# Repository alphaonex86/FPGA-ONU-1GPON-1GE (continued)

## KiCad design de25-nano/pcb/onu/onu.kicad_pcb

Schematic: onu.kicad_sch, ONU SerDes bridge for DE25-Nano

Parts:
C1, C3, C6, C9, C24, C25, C30, C48, C49, C50, C51, C54, C57, C60, C63, C65, C76, C77, C83, C85: 10u; C_0603_1608Metric
C2, C4, C5, C7, C8, C10, C11: 22u; C_0805_2012Metric
C12, C13, C66, C67: 1u; C_0402_1005Metric
C14, C15, C16, C17, C18, C19, C20, C21, C22, C23, C26, C27, C28, C29, C31, C32, C33, C34, C35, C36, C37, C38, C39, C40, C41, C42, C43, C44, C45, C46, C47, C52, C53, C55, C56, C58, C59, C61, C62, C64, C68, C69, C70, C71, C72, C73, C74, C75, C78, C79, C80, C81, C82, C84, C93, C94: 100n; C_0402_1005Metric
C86, C87: 100n; C_0603_1608Metric; MPN 100 V X7R
C88: 220p; C_0603_1608Metric; MPN 100 V X7R
C89: 47n; C_0402_1005Metric
C90: 2.2u; C_0603_1608Metric
C91, C92: 10p; C_0402_1005Metric
D1: BAT46WJ; D_SOD-323F; MPN BAT46WJ (100 V)
FB1, FB2, FB3, FB4, FB5, FB6, FB7, FB8, FB9: 120R@100MHz; L_0603_1608Metric; MPN BLM18PG121SN1D
H1, H2: M3; MountingHole_3.2mm_M3
J1: DE25-Nano GPIO; PinSocket_2x20_P2.54mm_Vertical
J2: JTAG; PinHeader_1x06_P2.54mm_Vertical
J3: OLT-ONU link; PinHeader_1x08_P2.54mm_Vertical
L1, L2: 2.2u; L_Cenker_CKCS252012; MPN CKCS252012-2R2M
L3: 4.7u; L_Cenker_CKCS252012; MPN 4.7 uH, Isat >= 1 A, 2520
R1, R3: 100k; R_0402_1005Metric
R2, R4: 120k; R_0402_1005Metric
R5, R6, R7, R8, R9, R12, R13, R14, R19, R20: 4.7k; R_0402_1005Metric
R10, R15, R16, R24, R26, R37, R43: 10k; R_0402_1005Metric
R11, R30, R35: 1k; R_0402_1005Metric
R17, R18: 0; R_0402_1005Metric
R21: 5.1k; R_0402_1005Metric
R22: 6.2k; R_0402_1005Metric
R23, R38: 20k; R_0402_1005Metric
R25: 12k; R_0402_1005Metric
R27: 5.6k; R_0402_1005Metric
R28: 3.9k; R_0402_1005Metric
R29, R41: 1.5k; R_0402_1005Metric
R31, R33, R40: 10; R_0402_1005Metric
R32: 15; R_0402_1005Metric
R34: 100; R_0402_1005Metric
R36: 300k; R_0603_1608Metric
R39: 33k; R_0402_1005Metric
R42: 3.01k; R_0402_1005Metric
RN1, RN2, RN3, RN4, RN5: 22; R_Array_Convex_4x0402; MPN 4D02WGJ0220TCE
U1, U2: TLV62569DBVR; SOT-23-5; MPN TLV62569DBVR
U3: TLV75525PDBVR; SOT-23-5; MPN TLV75525PDBVR
U4: LFE5UM-25F-6BG381C; Lattice_caBGA-381_17x17mm_Layout20x20_P0.8mm; MPN LFE5UM-25F-6BG381C
U5: SY88236LMG; QFN-32-1EP_5x5mm_P0.5mm_EP3.1x3.1mm_ThermalVias; MPN SY88236LMG
U6: SN65LVDT2DBVR; SOT-23-5; MPN SN65LVDT2DBVR
U7: BOSA GPON (X100DG); BOSA_GPON; MPN desoldered from an X100DG; pad order to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
U8: TPS61391RTER; WQFN-16-1EP_3x3mm_P0.5mm_EP1.68x1.68mm_ThermalVias; MPN TPS61391RTER
U9: AD5593RBRUZ; TSSOP-16_4.4x5mm_P0.65mm; MPN AD5593RBRUZ
Y1: SiT3821 155.52 MHz; Oscillator_SMD_SiTime_SiT9121-6Pin_3.2x2.5mm; MPN SiT3821AI-2B2-33NB155.520000 (LVDS, +-5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

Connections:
+1V1: C7.1, C8.1, C14.1, C15.1, C16.1, C17.1, C18.1, C19.1, C20.1, C21.1, C22.1, C23.1, C24.1, C25.1, L1.2, R1.1, U4.H8 (VCC), U4.H9 (VCC), U4.H10 (VCC), U4.H11 (VCC), U4.H12 (VCC), U4.H13 (VCC), U4.J8 (VCC), U4.J13 (VCC), U4.K8 (VCC), U4.K13 (VCC), U4.L8 (VCC), U4.L13 (VCC), U4.M8 (VCC), U4.M13 (VCC), U4.N8 (VCC), U4.N9 (VCC), U4.N10 (VCC), U4.N11 (VCC), U4.N12 (VCC), U4.N13 (VCC)
+1V1_HRX: C58.1, C59.1, C60.1, FB4.2, U4.T8 (VCCHRX0_D0CH0), U4.T9 (VCCHRX1_D0CH1)
+1V1_HTX: C55.1, C56.1, C57.1, FB3.2, U4.T7 (VCCHTX0_D0CH0), U4.T10 (VCCHTX1_D0CH1)
+1V1_SD: C10.1, C11.1, FB2.1, FB3.1, FB4.1, L2.2, R3.1
+1V1_VCCA: C52.1, C53.1, C54.1, FB2.2, U4.T6 (VCCA0), U4.U6 (VCCA0)
+2V5: C13.1, FB1.1, FB5.1, U3.5 (OUT)
+2V5_AUX: C26.1, C27.1, C28.1, C29.1, C30.1, FB1.2, U4.F6 (VCCAUX), U4.F15 (VCCAUX), U4.P6 (VCCAUX), U4.P15 (VCCAUX)
+2V5_AUXA: C61.1, C62.1, C63.1, FB5.2, U4.V10 (VCCAUXA0), U4.V11 (VCCAUXA0)
+3V3: C3.1, C4.1, C5.1, C12.1, C31.1, C32.1, C33.1, C34.1, C35.1, C36.1, C37.1, C38.1, C39.1, C40.1, C41.1, C42.1, C43.1, C44.1, C45.1, C46.1, C47.1, C48.1, C49.1, C50.1, C51.1, C94.1, FB6.1, FB7.1, FB9.1, J1.29, J2.1, R5.2, R6.2, R7.2, R8.2, R9.2, R10.2, R11.2, R12.2, R13.2, R19.2, R20.2, R43.2, U3.1 (IN), U3.3 (EN), U4.F9 (VCCIO0), U4.F10 (VCCIO0), U4.F11 (VCCIO1), U4.F12 (VCCIO1), U4.H6 (VCCIO7), U4.H7 (VCCIO7), U4.H14 (VCCIO2), U4.H15 (VCCIO2), U4.J6 (VCCIO7), U4.J15 (VCCIO2), U4.L6 (VCCIO6), U4.L7 (VCCIO6), U4.L14 (VCCIO3), U4.L15 (VCCIO3), U4.M6 (VCCIO6), U4.M15 (VCCIO3), U4.P9 (VCCIO8), U4.P10 (VCCIO8), U9.3 (V_{DD}), U9.9 (V_{LOGIC})
+3V3_APD: C84.1, C85.1, FB9.2, L3.1, R40.1, U8.10 (VIN), U8.13 (EN)
+3V3_APDA: C90.1, R40.2, U8.14 (AVCC), U8.15 (AVCC)
+3V3_OPT: C72.1, C73.1, C74.1, C75.1, C76.1, C77.1, C78.1, FB7.2, FB8.1, R21.2, R32.2, U5.17 (VCC), U5.20 (VCC), U5.32 (VCC), U6.1 (VCC), U7.T1 (LD_A), U7.T4 (MPD_K)
+3V3_RX: C81.1, C82.1, C83.1, FB8.2, U7.R2 (VCC)
+3V3_XO: C64.1, C65.1, FB6.2, Y1.6 (VDD)
+5V: C1.1, C2.1, C6.1, C9.1, J1.11, U1.1 (EN), U1.4 (VIN), U2.1 (EN), U2.4 (VIN)
APCFAULT_N: U5.25 (~APCFAULT), U9.13 (IO7)
APCSET: R23.1, R24.1, U5.12 (APCSET)
APC_ADJ: R24.2, U9.4 (IO0)
APD_ADJ: R38.2, U9.6 (IO2)
APD_CAP: C89.1, U8.9 (CAP)
APD_FB: R36.2, R37.1, R38.1, U8.12 (FB)
APD_ISHORT: R39.1, U8.11 (ISHORT)
APD_MON: C91.1, R41.1, U8.4 (MON1), U9.11 (IO5)
APD_MON2: C92.1, R42.1, U8.3 (MON2)
BEN0: J1.15, U4.A13 (PT40B)
BEN1: J1.17, U4.A12 (PT40A)
BEN2: J1.19, U4.A11 (PT27B/PCLKC0_1)
BEN3: J1.20, U4.B10 (PT24B/GR_PCLK0_0)
BEN4: J1.21, U4.A8 (PT18B)
BEN5: J1.22, U4.B9 (PT22A)
BEN6: J1.24, U4.B8 (PT15B)
BEN7: J1.26, U4.A7 (PT18A)
BEN_N: R18.1, U4.W9 (HDTXN0_D0CH1)
BEN_P: R17.1, U4.W8 (HDTXP0_D0CH1)
BIASMAX: R27.1, U5.14 (BIASMAX)
BIASMON: R29.1, U5.23 (BIASMON), U9.7 (IO3)
CCLK: J3.4, R11.1, U4.U3 (CCLK)
CFG0: R5.1, U4.U4 (CFG_0)
DDM_RESET: R43.1, U9.1 (~RESET)
DDM_VREF: C93.1, U9.8 (V_{REF})
DONE: R8.1, U4.Y3 (DONE)
DS0: J1.13, RN4.5 (R4.2)
DS0_S: RN4.4 (R4.1), U4.A14 (PT47A)
DS1: J1.14, RN4.6 (R3.2)
DS1_S: RN4.3 (R3.1), U4.B13 (PT42A)
DS2: J1.16, RN4.7 (R2.2)
DS2_S: RN4.2 (R2.1), U4.B12 (PT35A/PCLKT1_0)
DS3: J1.18, RN4.8 (R1.2)
DS3_S: RN4.1 (R1.1), U4.B11 (PT29A/PCLKT0_0)
DS4: J1.23, RN3.5 (R4.2)
DS4_S: RN3.4 (R4.1), U4.A9 (PT24A/GR_PCLK0_1)
DS5: J1.27, RN3.6 (R3.2)
DS5_S: RN3.3 (R3.1), U4.B6 (PT4B)
DS6: J1.28, RN3.7 (R2.2)
DS6_S: RN3.2 (R2.1), U4.A6 (PT4A)
DS7: J1.31, RN3.8 (R1.2)
DS7_S: RN3.1 (R1.1), U4.B5 (PL2C)
DS8: J1.32, RN2.5 (R4.2)
DS8_S: RN2.4 (R4.1), U4.A5 (PL2B)
DS9: J1.33, RN2.6 (R3.2)
DS9_S: RN2.3 (R3.1), U4.B4 (PL5B)
DS10: J1.34, RN2.7 (R2.2)
DS10_S: RN2.2 (R2.1), U4.A4 (PL2A)
DS11: J1.35, RN2.8 (R1.2)
DS11_S: RN2.1 (R1.1), U4.B3 (PL5D)
DS12: J1.36, RN1.5 (R4.2)
DS12_S: RN1.4 (R4.1), U4.A3 (PL5C)
DS13: J1.37, RN1.6 (R3.2)
DS13_S: RN1.3 (R3.1), U4.B2 (PL14C/VREF1_7)
DS14: J1.38, RN1.7 (R2.2)
DS14_S: RN1.2 (R2.1), U4.A2 (PL14A)
DS15: J1.39, RN1.8 (R1.2)
DS15_S: RN1.1 (R1.1), U4.B1 (PL14B)
DS_CLK: J1.1, RN5.7 (R2.2)
DS_CLK_S: RN5.2 (R2.1), U4.B20 (PT67B)
FB_1V1: R1.2, R2.1, U1.5 (FB)
FB_1V1_SD: R3.2, R4.1, U2.5 (FB)
GND: C1.2, C2.2, C3.2, C4.2, C5.2, C6.2, C7.2, C8.2, C9.2, C10.2, C11.2, C12.2, C13.2, C14.2, C15.2, C16.2, C17.2, C18.2, C19.2, C20.2, C21.2, C22.2, C23.2, C24.2, C25.2, C26.2, C27.2, C28.2, C29.2, C30.2, C31.2, C32.2, C33.2, C34.2, C35.2, C36.2, C37.2, C38.2, C39.2, C40.2, C41.2, C42.2, C43.2, C44.2, C45.2, C46.2, C47.2, C48.2, C49.2, C50.2, C51.2, C52.2, C53.2, C54.2, C55.2, C56.2, C57.2, C58.2, C59.2, C60.2, C61.2, C62.2, C63.2, C64.2, C65.2, C66.2, C67.2, C72.2, C73.2, C74.2, C75.2, C76.2, C77.2, C78.2, C81.2, C82.2, C83.2, C84.2, C85.2, C86.2, C87.2, C88.2, C89.2, C90.2, C91.2, C92.2, C93.2, C94.2, J1.12, J1.30, J2.6, J3.1, J3.8, R2.2, R4.2, R14.2, R22.2, R23.2, R25.2, R27.2, R28.2, R29.2, R30.2, R37.2, R39.2, R41.2, R42.2, U1.2 (GND), U2.2 (GND), U3.2 (GND), U4.B7 (GND), U4.B14 (GND), U4.C19 (GND), U4.D4 (GND), U4.F7 (GND), U4.F8 (GND), U4.F13 (GND), U4.F14 (GND), U4.G4 (GND), U4.G6 (GND), U4.G7 (GND), U4.G8 (GND), U4.G9 (GND), U4.G10 (GND), U4.G11 (GND), U4.G12 (GND), U4.G13 (GND), U4.G14 (GND), U4.G15 (GND), U4.G17 (GND), U4.H19 (GND), U4.J2 (GND), U4.J7 (GND), U4.J9 (GND), U4.J10 (GND), U4.J11 (GND), U4.J12 (GND), U4.J14 (GND), U4.K6 (GND), U4.K7 (GND), U4.K9 (GND), U4.K10 (GND), U4.K11 (GND), U4.K12 (GND), U4.K14 (GND), U4.K15 (GND), U4.L9 (GND), U4.L10 (GND), U4.L11 (GND), U4.L12 (GND), U4.M2 (GND), U4.M7 (GND), U4.M9 (GND), U4.M10 (GND), U4.M11 (GND), U4.M12 (GND), U4.M14 (GND), U4.M16 (GND), U4.N6 (GND), U4.N7 (GND), U4.N14 (GND), U4.N15 (GND), U4.P7 (GND), U4.P8 (GND), U4.P11 (GND), U4.P12 (GND), U4.P13 (GND), U4.P14 (GND), U4.R4 (CFG_2), U4.R19 (GND), U4.T4 (CFG_1), U4.U7 (GND), U4.U8 (GND), U4.U9 (GND), U4.U10 (GND), U4.U11 (GND), U4.U12 (GND), U4.U13 (GND), U4.U14 (GND), U4.V5 (GND), U4.V6 (GND), U4.V7 (GND), U4.V8 (GND), U4.V9 (GND), U4.V12 (GND), U4.V13 (GND), U4.V14 (GND), U4.V15 (GND), U4.V16 (GND), U4.V19 (GND), U4.V20 (GND), U4.W6 (GND), U4.W7 (GND), U4.W12 (GND), U4.W15 (GND), U4.W16 (GND), U4.W19 (GND), U4.Y7 (HDRXP0_D0CH1), U4.Y8 (HDRXN0_D0CH1), U5.1 (LOS/SD_SEL), U5.5 (GND), U5.8 (GND), U5.16 (GND), U5.24 (GND), U5.29 (GND), U5.33 (EP), U6.2 (GND), U7.R5 (GND), U8.7 (GND), U8.16 (AGND), U8.17 (EP), U9.2 (A0), U9.14 (GND), Y1.3 (GND)
HOLDN: R10.1, U4.R2 (PB15A/HOLDN/DI/BUSY/CSSPIN/CEN)
HV_APD: C88.1, U7.R1 (VAPD), U8.5 (APD)
HV_FILT: C87.1, R34.2, R35.1
HV_MONIN: R35.2, U8.6 (MONIN)
HV_OUT: C86.1, D1.1 (K), R34.1, R36.1
HV_SW: D1.2 (A), L3.2, U8.8 (SW)
INITN: R7.1, U4.V3 (INITN)
LASER_DIS: R19.1, U4.U17 (PR47B), U5.11 (TXDIS)
LD_BEN: U5.9 (BEN+), U6.5 (R)
LD_BEN_N: R22.1, U5.10 (BEN-)
LD_BIAS: R33.1, U5.21 (BIAS)
LD_K: R31.2, R33.2, U7.T2 (LD_K)
LD_MD: U5.22 (MD), U7.T3 (MPD_A)
LD_MODN: R32.1, U5.18 (MOD-)
LD_MODP: R31.1, U5.19 (MOD+)
LOSLVL: R21.1, U5.2 (LOSLVL)
MISO: J3.6, U4.V2 (PB11A/D1/MISO/IO1)
MODMON: R28.1, U5.15 (MODMON), U9.10 (IO4)
MODSET: R25.1, R26.1, U5.13 (MODSET)
MOD_ADJ: R26.2, U9.5 (IO1)
MOSI: J3.5, U4.W2 (PB11B/D0/MOSI/IO0)
ONU_BEN_N: R18.2, U6.4 (B)
ONU_BEN_P: R17.2, U6.3 (A)
ONU_PROGRAMN: J3.7, R6.1, U4.W3 (PROGRAMN)
ONU_RD_N: C71.1, U5.30 (ROUT-)
ONU_RD_P: C70.1, U5.31 (ROUT+)
ONU_SCL: J3.2, U9.16 (SCL)
ONU_SDA: J3.3, U9.15 (SDA)
ONU_TD_N: C69.2, U5.6 (DIN+)
ONU_TD_P: C68.2, U5.7 (DIN-)
REFCLK_N: U4.Y12 (REFCLKN_D0), Y1.5 (OUT-)
REFCLK_P: U4.Y11 (REFCLKP_D0), Y1.4 (OUT+)
RIN_N: C80.2, U5.28 (RIN-)
RIN_P: C79.2, U5.27 (RIN+)
RSSI: R30.1, U5.26 (RSSI), U9.12 (IO6)
RX0_N: C71.2, U4.Y6 (HDRXN0_D0CH0)
RX0_P: C70.2, U4.Y5 (HDRXP0_D0CH0)
RX_SD: R20.1, U4.T17 (PR47D/LRC_GPLL0C_IN), U5.3 (LOS/SD), U5.4 (~JAM)
SN: J1.40, R9.1, U4.T2 (PB13A/SN/CSN)
SW_1V1: L1.1, U1.3 (SW)
SW_1V1_SD: L2.1, U2.3 (SW)
TCK: J2.2, R14.1, U4.T5 (TCK)
TDI: J2.3, R12.1, U4.R5 (TDI)
TDO: J2.4, U4.V4 (TDO)
TIA_N: C80.1, U7.R4 (OUT-)
TIA_P: C79.1, U7.R3 (OUT+)
TMS: J2.5, R13.1, U4.U5 (TMS)
TX0_N: C69.1, U4.W5 (HDTXN0_D0CH0)
TX0_P: C68.1, U4.W4 (HDTXP0_D0CH0)
TX_CLK: J1.3, RN5.8 (R1.2)
TX_CLK_S: RN5.1 (R1.1), U4.A19 (PT67A)
US0: J1.2, U4.B19 (PT65B)
US1: J1.4, U4.B18 (PT62B)
US2: J1.5, U4.A18 (PT65A)
US3: J1.6, U4.B17 (PT60A)
US4: J1.7, U4.A17 (PT62A)
US5: J1.8, U4.B16 (PT56B)
US6: J1.9, U4.A16 (PT56A)
US7: J1.10, U4.B15 (PT51A)
US_CLK: J1.25, U4.A10 (PT27A/PCLKT0_1)
VCXO_PWM: R15.1, U4.U16 (PR47C/LRC_GPLL0T_IN)
VCXO_RC: C66.1, R15.2, R16.1
VCXO_VC: C67.1, R16.2, Y1.1 (VIN)

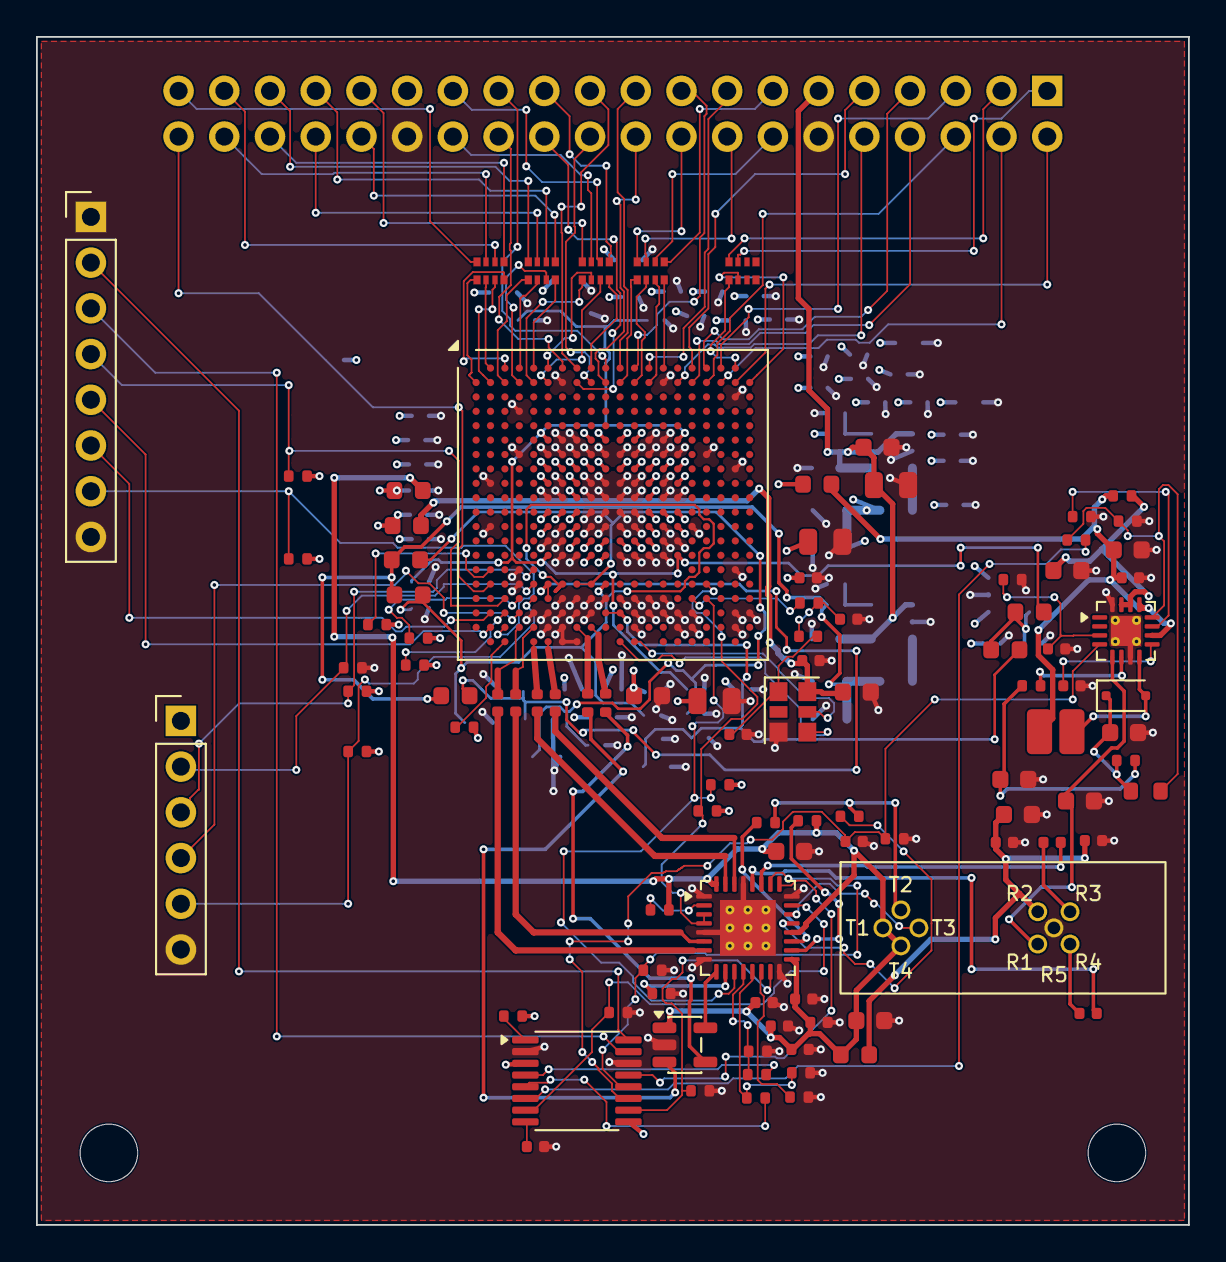
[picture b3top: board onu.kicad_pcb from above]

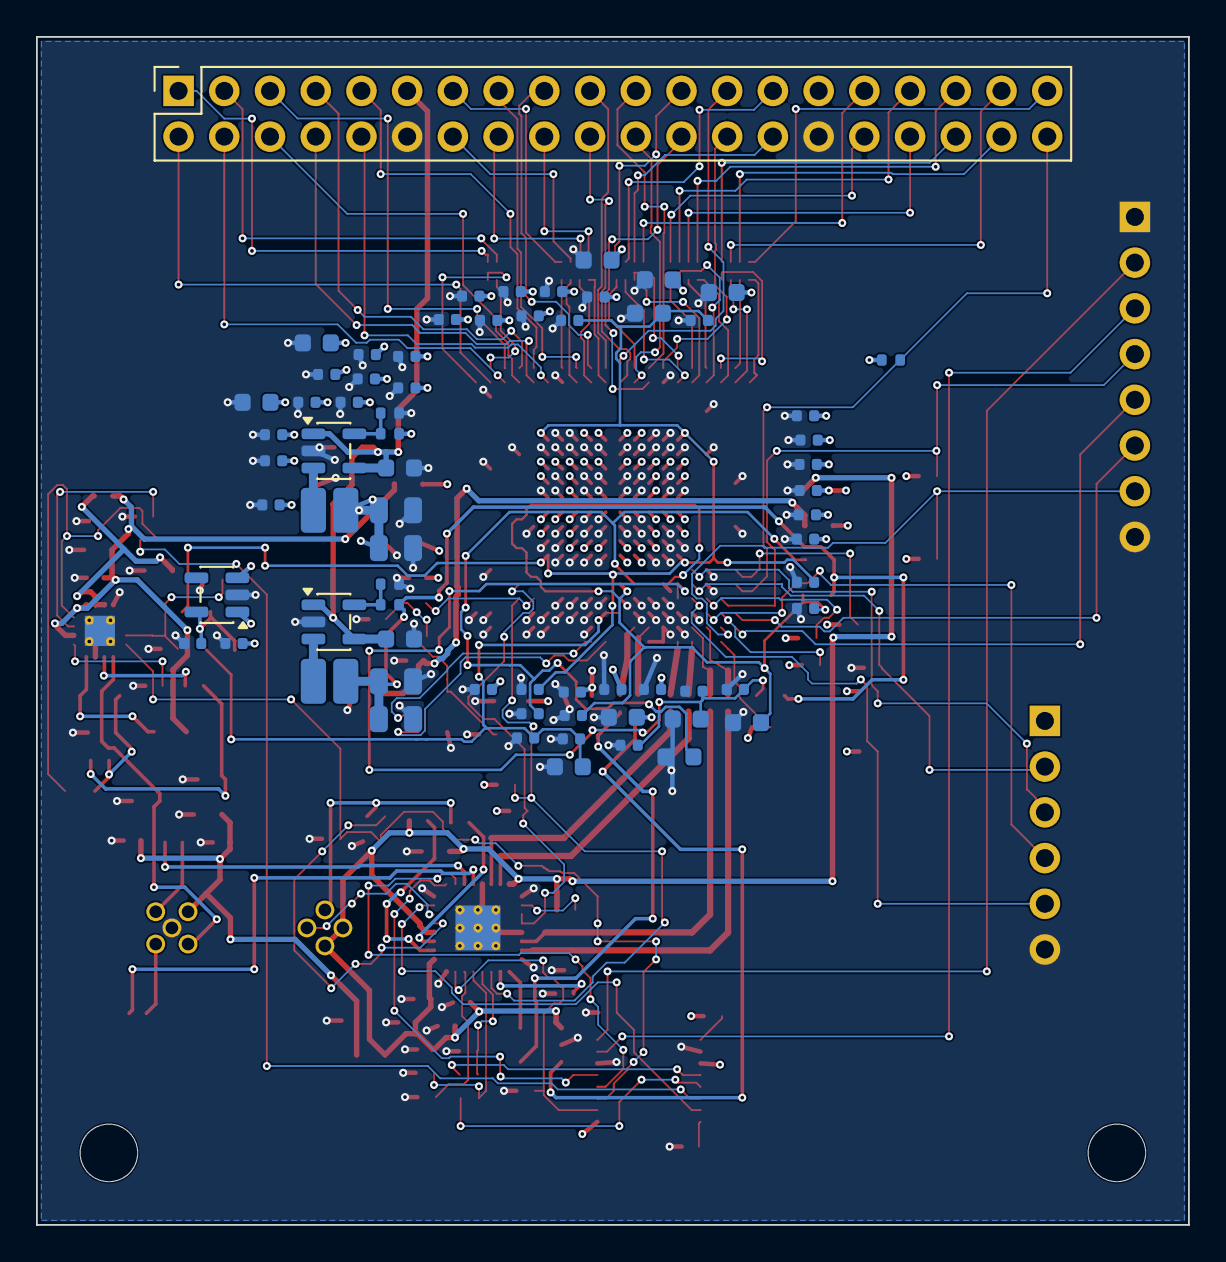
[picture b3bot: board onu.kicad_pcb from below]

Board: 4 copper layers, 64.0 x 66.0 mm, 170 parts (69 on the bottom side), 141 nets.

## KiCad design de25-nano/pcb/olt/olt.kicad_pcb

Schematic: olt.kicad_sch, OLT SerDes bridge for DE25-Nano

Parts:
C1, C3, C6, C9, C24, C25, C30, C48, C49, C50, C51, C54, C57, C60, C63, C66, C72, C74: 10u; C_0603_1608Metric
C2, C4, C5, C7, C8, C10, C11, C75: 22u; C_0805_2012Metric
C12, C13: 1u; C_0402_1005Metric
C14, C15, C16, C17, C18, C19, C20, C21, C22, C23, C26, C27, C28, C29, C31, C32, C33, C34, C35, C36, C37, C38, C39, C40, C41, C42, C43, C44, C45, C46, C47, C52, C53, C55, C56, C58, C59, C61, C62, C64, C65, C67, C68, C69, C70, C71, C73: 100n; C_0402_1005Metric
FB1, FB2, FB3, FB4, FB5, FB6: 120R@100MHz; L_0603_1608Metric; MPN BLM18PG121SN1D
H1, H2: M3; MountingHole_3.2mm_M3
J1: DE25-Nano GPIO; PinSocket_2x20_P2.54mm_Vertical
J2: JTAG; PinHeader_1x06_P2.54mm_Vertical
J3: SFP cage; Connector_SFP_and_Cage; MPN TE 1367073-1 + cage 2227302-1
J4: OLT-ONU link; PinHeader_1x08_P2.54mm_Vertical
L1, L2: 2.2u; L_Cenker_CKCS252012; MPN SLO252012F2R2MTT
L3, L4: 1u; L_0805_2012Metric; MPN 1 uH >= 1 A, low DCR
R1, R3: 100k; R_0402_1005Metric
R2, R4: 120k; R_0402_1005Metric
R5, R6, R7, R8, R9, R12, R13, R14, R21, R22, R27, R28, R29, R30, R31, R32: 4.7k; R_0402_1005Metric
R10, R15, R16, R17, R20, R23, R24: 10k; R_0402_1005Metric
R11: 1k; R_0402_1005Metric
R18, R19: 2.2k; R_0402_1005Metric
R25: 33; R_0402_1005Metric
R26: 330; R_0402_1005Metric
RN1, RN2, RN3: 22; R_Array_Convex_4x0402; MPN 4D02WGJ0220TCE
U1, U2: TLV62569DBVR; SOT-23-5; MPN TLV62569DBVR
U3: TLV75525PDBVR; SOT-23-5; MPN TLV75525PDBVR
U4: LFE5UM-25F-6BG381C; Lattice_caBGA-381_17x17mm_Layout20x20_P0.8mm; MPN LFE5UM-25F-6BG381C
U5: PCA9555PW; TSSOP-24_4.4x7.8mm_P0.65mm; MPN PCA9555PW
U6: PCA9540BD; SOIC-8_3.9x4.9mm_P1.27mm; MPN PCA9540BD
U7, U8: SN74LVC1G125DBVR; SOT-23-5; MPN SN74LVC1G125DBVR
Y1: SiT9121 155.52 MHz; Oscillator_SMD_SiTime_SiT9121-6Pin_3.2x2.5mm; MPN SiT9121AI-2B3-33E155.52000 (LVDS; check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
Y2: SiT9121 125 MHz; Oscillator_SMD_SiTime_SiT9121-6Pin_3.2x2.5mm; MPN SiT9121AI-2B3-33E125000 (LVDS; check co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

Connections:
+1V1: C7.1, C8.1, C14.1, C15.1, C16.1, C17.1, C18.1, C19.1, C20.1, C21.1, C22.1, C23.1, C24.1, C25.1, L1.2, R1.1, U4.H8 (VCC), U4.H9 (VCC), U4.H10 (VCC), U4.H11 (VCC), U4.H12 (VCC), U4.H13 (VCC), U4.J8 (VCC), U4.J13 (VCC), U4.K8 (VCC), U4.K13 (VCC), U4.L8 (VCC), U4.L13 (VCC), U4.M8 (VCC), U4.M13 (VCC), U4.N8 (VCC), U4.N9 (VCC), U4.N10 (VCC), U4.N11 (VCC), U4.N12 (VCC), U4.N13 (VCC)
+1V1_HRX: C58.1, C59.1, C60.1, FB4.2, U4.T8 (VCCHRX0_D0CH0)
+1V1_HTX: C55.1, C56.1, C57.1, FB3.2, U4.T7 (VCCHTX0_D0CH0), U4.T10 (VCCHTX1_D0CH1)
+1V1_SD: C10.1, C11.1, FB2.1, FB3.1, FB4.1, L2.2, R3.1
+1V1_VCCA: C52.1, C53.1, C54.1, FB2.2, U4.T6 (VCCA0), U4.U6 (VCCA0)
+2V5: C13.1, FB1.1, FB5.1, U3.5 (OUT)
+2V5_AUX: C26.1, C27.1, C28.1, C29.1, C30.1, FB1.2, U4.F6 (VCCAUX), U4.F15 (VCCAUX), U4.P6 (VCCAUX), U4.P15 (VCCAUX)
+2V5_AUXA: C61.1, C62.1, C63.1, FB5.2, U4.V10 (VCCAUXA0), U4.V11 (VCCAUXA0)
+3V3: C3.1, C4.1, C5.1, C12.1, C31.1, C32.1, C33.1, C34.1, C35.1, C36.1, C37.1, C38.1, C39.1, C40.1, C41.1, C42.1, C43.1, C44.1, C45.1, C46.1, C47.1, C48.1, C49.1, C50.1, C51.1, C67.1, C68.1, C69.1, C70.1, C75.1, FB6.1, J1.29, J2.1, L3.1, L4.1, R5.2, R6.2, R7.2, R8.2, R9.2, R10.2, R11.2, R12.2, R13.2, R15.2, R16.2, R18.2, R19.2, R20.2, R21.2, R22.2, R23.2, R24.2, R27.2, R28.2, R29.2, R30.2, R31.2, R32.2, U3.1 (IN), U3.3 (EN), U4.F9 (VCCIO0), U4.F10 (VCCIO0), U4.F11 (VCCIO1), U4.F12 (VCCIO1), U4.H6 (VCCIO7), U4.H7 (VCCIO7), U4.H14 (VCCIO2), U4.H15 (VCCIO2), U4.J6 (VCCIO7), U4.J15 (VCCIO2), U4.L6 (VCCIO6), U4.L7 (VCCIO6), U4.L14 (VCCIO3), U4.L15 (VCCIO3), U4.M6 (VCCIO6), U4.M15 (VCCIO3), U4.P9 (VCCIO8), U4.P10 (VCCIO8), U5.24 (VDD), U6.3 (VDD), U7.5 (VCC), U8.5 (VCC)
+3V3_SFPR: C73.1, C74.1, J3.15 (VccR), L4.2
+3V3_SFPT: C71.1, C72.1, J3.16 (VccT), L3.2
+3V3_XO: C64.1, C65.1, C66.1, FB6.2, Y1.6 (VDD), Y2.6 (VDD)
+5V: C1.1, C2.1, C6.1, C9.1, J1.11, U1.1 (EN), U1.4 (VIN), U2.1 (EN), U2.4 (VIN)
AUX: J1.16, RN1.8 (R1.2)
AUX_S: RN1.1 (R1.1), U4.A10 (PT27A/PCLKT0_1)
CCLK: J1.37, J4.4, R11.1, U4.U3 (CCLK)
CFG0: R5.1, U4.U4 (CFG_0)
DONE: R8.1, U4.Y3 (DONE)
DS0: J1.3, U4.B18 (PT62B)
DS1: J1.13, U4.A12 (PT40A)
DS2: J1.14, U4.B11 (PT29A/PCLKT0_0)
DS3: J1.15, U4.A11 (PT27B/PCLKC0_1)
DS4: J1.23, U4.A9 (PT24A/GR_PCLK0_1)
DS5: J1.24, U4.A8 (PT18B)
DS6: J1.25, U4.A7 (PT18A)
DS7: J1.26, U4.B6 (PT4B)
DS8: J1.27, U4.A6 (PT4A)
DS9: J1.28, U4.A5 (PL2B)
DS10: J1.31, U4.B4 (PL5B)
DS11: J1.32, U4.A4 (PL2A)
DS12: J1.33, U4.A3 (PL5C)
DS13: J1.34, U4.B2 (PL14C/VREF1_7)
DS14: J1.35, U4.A2 (PL14A)
DS15: J1.36, U4.B1 (PL14B)
DS_CLK: J1.22, U4.B12 (PT35A/PCLKT1_0)
FB_1V1: R1.2, R2.1, U1.5 (FB)
FB_1V1_SD: R3.2, R4.1, U2.5 (FB)
GND: C1.2, C2.2, C3.2, C4.2, C5.2, C6.2, C7.2, C8.2, C9.2, C10.2, C11.2, C12.2, C13.2, C14.2, C15.2, C16.2, C17.2, C18.2, C19.2, C20.2, C21.2, C22.2, C23.2, C24.2, C25.2, C26.2, C27.2, C28.2, C29.2, C30.2, C31.2, C32.2, C33.2, C34.2, C35.2, C36.2, C37.2, C38.2, C39.2, C40.2, C41.2, C42.2, C43.2, C44.2, C45.2, C46.2, C47.2, C48.2, C49.2, C50.2, C51.2, C52.2, C53.2, C54.2, C55.2, C56.2, C57.2, C58.2, C59.2, C60.2, C61.2, C62.2, C63.2, C64.2, C65.2, C66.2, C67.2, C68.2, C69.2, C70.2, C71.2, C72.2, C73.2, C74.2, C75.2, J1.12, J1.30, J2.6, J3.1 (VeeT), J3.10 (VeeR), J3.11 (VeeR), J3.14 (VeeR), J3.17 (VeeT), J3.20 (VeeT), J3.CAGE, J4.1, J4.8, R2.2, R4.2, R14.2, R17.2, U1.2 (GND), U2.2 (GND), U3.2 (GND), U4.B7 (GND), U4.B14 (GND), U4.C19 (GND), U4.D4 (GND), U4.F7 (GND), U4.F8 (GND), U4.F13 (GND), U4.F14 (GND), U4.G4 (GND), U4.G6 (GND), U4.G7 (GND), U4.G8 (GND), U4.G9 (GND), U4.G10 (GND), U4.G11 (GND), U4.G12 (GND), U4.G13 (GND), U4.G14 (GND), U4.G15 (GND), U4.G17 (GND), U4.H19 (GND), U4.J2 (GND), U4.J7 (GND), U4.J9 (GND), U4.J10 (GND), U4.J11 (GND), U4.J12 (GND), U4.J14 (GND), U4.K6 (GND), U4.K7 (GND), U4.K9 (GND), U4.K10 (GND), U4.K11 (GND), U4.K12 (GND), U4.K14 (GND), U4.K15 (GND), U4.L9 (GND), U4.L10 (GND), U4.L11 (GND), U4.L12 (GND), U4.M2 (GND), U4.M7 (GND), U4.M9 (GND), U4.M10 (GND), U4.M11 (GND), U4.M12 (GND), U4.M14 (GND), U4.M16 (GND), U4.N6 (GND), U4.N7 (GND), U4.N14 (GND), U4.N15 (GND), U4.P7 (GND), U4.P8 (GND), U4.P11 (GND), U4.P12 (GND), U4.P13 (GND), U4.P14 (GND), U4.R4 (CFG_2), U4.R19 (GND), U4.T4 (CFG_1), U4.U7 (GND), U4.U8 (GND), U4.U9 (GND), U4.U10 (GND), U4.U11 (GND), U4.U12 (GND), U4.U13 (GND), U4.U14 (GND), U4.V5 (GND), U4.V6 (GND), U4.V7 (GND), U4.V8 (GND), U4.V9 (GND), U4.V12 (GND), U4.V13 (GND), U4.V14 (GND), U4.V15 (GND), U4.V16 (GND), U4.V19 (GND), U4.V20 (GND), U4.W6 (GND), U4.W7 (GND), U4.W12 (GND), U4.W15 (GND), U4.W16 (GND), U4.W19 (GND), U4.Y7 (HDRXP0_D0CH1), U4.Y8 (HDRXN0_D0CH1), U5.2 (A1), U5.3 (A2), U5.12 (VSS), U5.21 (A0), U6.6 (VSS), U7.3 (GND), U8.3 (GND), Y1.3 (GND), Y2.3 (GND)
HOLDN: R10.1, U4.R2 (PB15A/HOLDN/DI/BUSY/CSSPIN/CEN)
INITN: R7.1, U4.V3 (INITN)
IRQ: J1.21, R20.1, U5.1 (~INT)
MISO: J1.40, J4.6, R15.1, U4.V2 (PB11A/D1/MISO/IO1)
MOSI: J1.39, J4.5, U4.W2 (PB11B/D0/MOSI/IO0)
OLT_PROGRAMN: R6.1, U4.W3 (PROGRAMN), U5.13 (IO1_0)
ONU_PROGRAMN: J4.7, U5.14 (IO1_1)
ONU_SCL: J4.2, R21.1, U6.8 (SC1)
ONU_SDA: J4.3, R22.1, U6.7 (SD1)
P7_BUF: R25.1, U7.4
P7_OE_N: R23.1, U5.8 (IO0_4), U7.1
P9_BUF: R26.1, U8.4
P9_OE_N: R24.1, U5.9 (IO0_5), U8.1
REF125_OE: R17.1, U5.11 (IO0_7), Y2.1 (OE)
REF155_OE: R16.1, U5.10 (IO0_6), Y1.1 (OE)
REFCLK_N: U4.Y12 (REFCLKN_D0), Y1.5 (OUT-), Y2.5 (OUT-)
REFCLK_P: U4.Y11 (REFCLKP_D0), Y1.4 (OUT+), Y2.4 (OUT+)
RSSI_TRIG: J1.18, U8.2
RX0_N: J3.12 (RD-), U4.Y6 (HDRXN0_D0CH0)
RX0_P: J3.13 (RD+), U4.Y5 (HDRXP0_D0CH0)
RX_RESET: J1.17, U7.2
SCL: J1.19, R18.1, U5.22 (SCL), U6.1 (SCL)
SDA: J1.20, R19.1, U5.23 (SDA), U6.2 (SDA)
SFP_LOS: J3.8 (RX_LOS), R29.1, U5.6 (IO0_2)
SFP_MOD_ABS: J3.6 (MOD_ABS), R30.1, U5.4 (IO0_0)
SFP_P7: J3.7 (RS0), R25.2
SFP_P9: J3.9 (RS1), R26.2
SFP_SCL: J3.5 (SCL), R31.1, U6.5 (SC0)
SFP_SDA: J3.4 (SDA), R32.1, U6.4 (SD0)
SFP_TX_DIS: J3.3 (TX_DISABLE), R28.1, U5.7 (IO0_3)
SFP_TX_FAULT: J3.2 (TX_FAULT), R27.1, U5.5 (IO0_1)
SN: J1.38, R9.1, U4.T2 (PB13A/SN/CSN)
SW_1V1: L1.1, U1.3 (SW)
SW_1V1_SD: L2.1, U2.3 (SW)
TCK: J2.2, R14.1, U4.T5 (TCK)
TDI: J2.3, R12.1, U4.R5 (TDI)
TDO: J2.4, U4.V4 (TDO)
TMS: J2.5, R13.1, U4.U5 (TMS)
TX0_N: J3.18 (TD+), U4.W5 (HDTXN0_D0CH0)
TX0_P: J3.19 (TD-), U4.W4 (HDTXP0_D0CH0)
TX_CLK: J1.1, RN3.7 (R2.2)
TX_CLK_S: RN3.2 (R2.1), U4.B19 (PT65B)
US0: J1.2, RN3.8 (R1.2)
US0_S: RN3.1 (R1.1), U4.A19 (PT67A)
US1: J1.4, RN2.5 (R4.2)
US1_S: RN2.4 (R4.1), U4.B17 (PT60A)
US2: J1.5, RN2.6 (R3.2)
US2_S: RN2.3 (R3.1), U4.A17 (PT62A)
US3: J1.6, RN2.7 (R2.2)
US3_S: RN2.2 (R2.1), U4.B16 (PT56B)
US4: J1.7, RN2.8 (R1.2)
US4_S: RN2.1 (R1.1), U4.B15 (PT51A)
US5: J1.8, RN1.5 (R4.2)
US5_S: RN1.4 (R4.1), U4.A14 (PT47A)
US6: J1.9, RN1.6 (R3.2)
US6_S: RN1.3 (R3.1), U4.B13 (PT42A)
US7: J1.10, RN1.7 (R2.2)
US7_S: RN1.2 (R2.1), U4.A13 (PT40B)

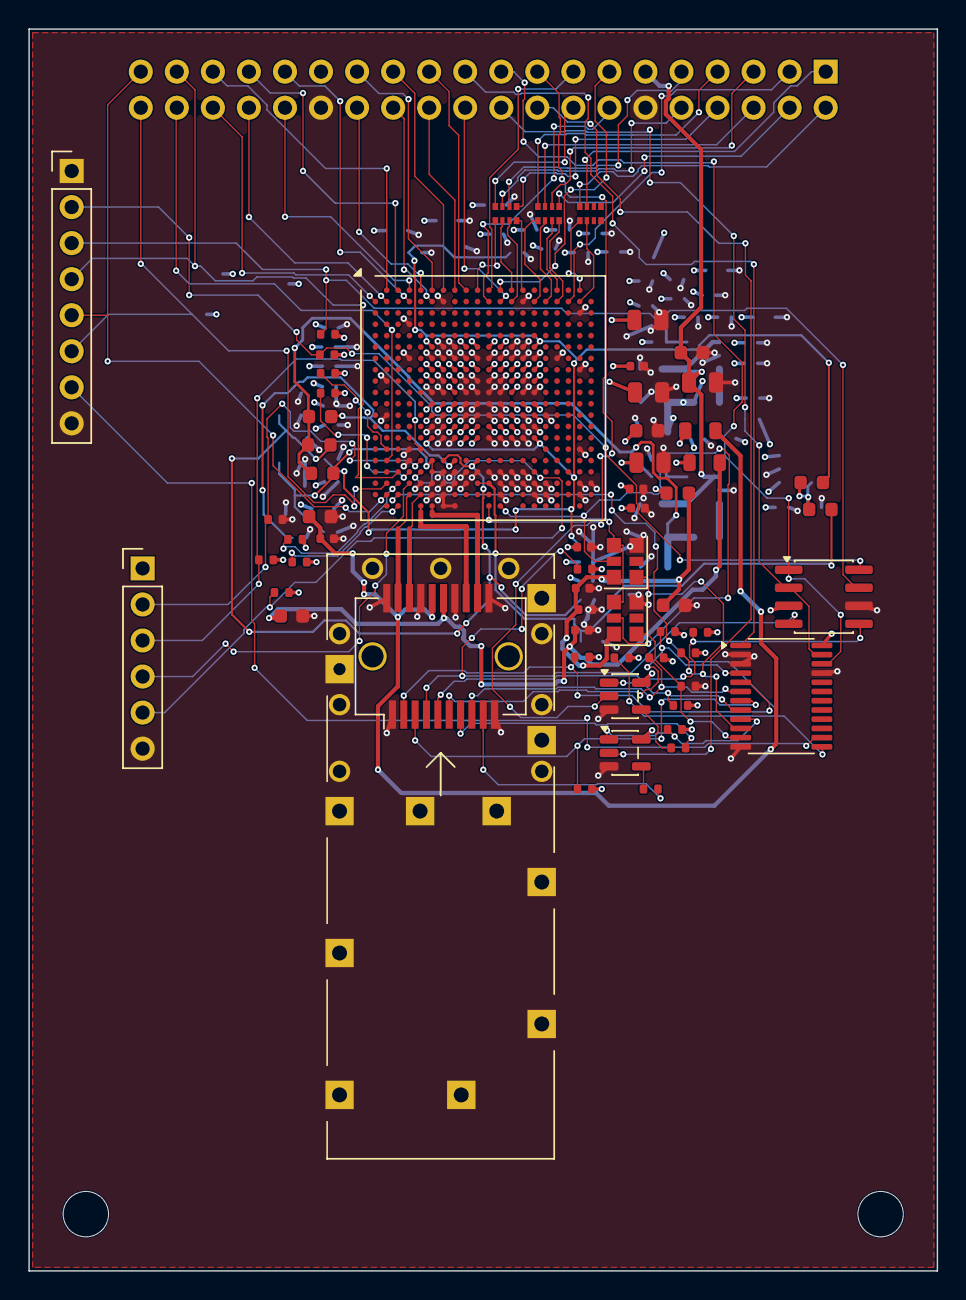
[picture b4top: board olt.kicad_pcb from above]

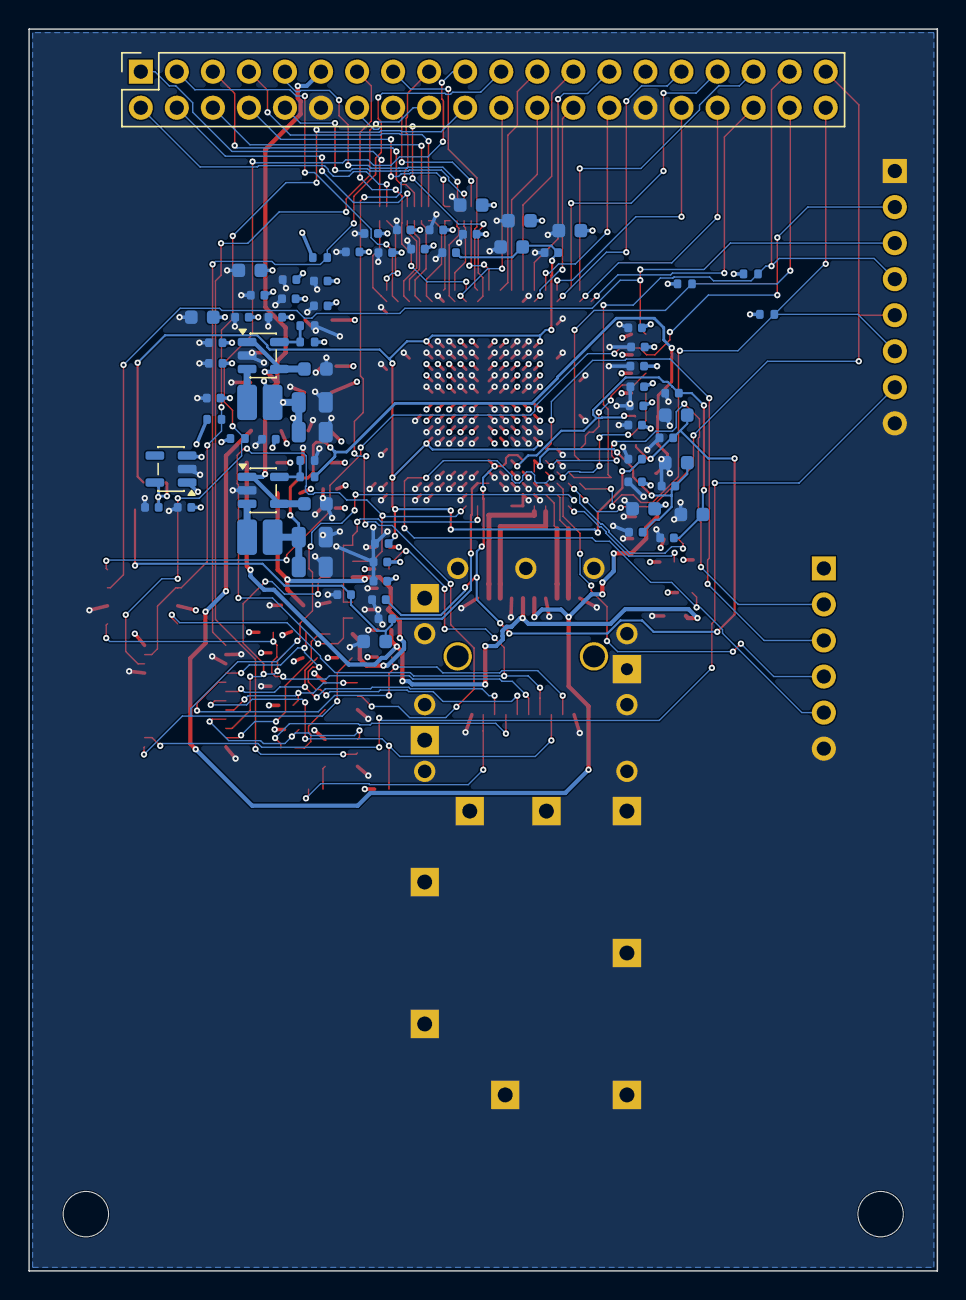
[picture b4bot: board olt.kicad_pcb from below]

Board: 4 copper layers, 64.0 x 87.5 mm, 136 parts (74 on the bottom side), 96 nets.

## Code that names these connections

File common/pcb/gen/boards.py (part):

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        cfg = {'CFG_0': 'GND', 'CFG_1': 'GND', 'CFG_2': 'GND', 'PROGRAMN': programn, 'INITN': 'INITN', 'DONE': 'DONE',
               'TCK': 'TCK', 'TDI': 'TDI', 'TDO': 'TDO', 'TMS': 'TMS', 'CCLK': spi[1]}
        cfg[f'CFG_{mode[-1]}'] = mode
        select, idle = ('HOLDN/DI/BUSY/CSSPIN/CEN', 'SN/CSN') if flash else ('SN/CSN', 'HOLDN/DI/BUSY/CSSPIN/CEN')
        dual = {select: spi[0], 'D0/MOSI/IO0': spi[2], 'D1/MISO/IO1': spi[3], idle: 'HOLDN'}
        for b, f in all_balls.items():
            if f in cfg: conn[b] = cfg[f]
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          {'A': 'ONU_BEN_P', 'B': 'ONU_BEN_N', 'R': 'LD_BEN', 'VCC': '+3V3_OPT', 'GND': 'GND'}, MPN='SN65LVDT2DBVR')
    b.decouple('+3V3_OPT', 1)
    b.r('6.2k', 'LD_BEN_N', 'GND')    # BEN- threshold for LVTTL on BEN+ (datasheet Fig. 2e)
    for pin, r_gnd, dac in (('APCSET', '20k', 'APC_ADJ'), ('MODSET', '12k', 'MOD_ADJ')):
        b.r(r_gnd, pin, 'GND'); b.r('10k', pin, dac)
    b.r('5.6k', 'BIASMAX', 'GND')
    b.r('3.9k', 'MODMON', 'GND'); b.r('1.5k', 'BIASMON', 'GND'); b.r('1k', 'RSSI', 'GND')   # <= 2.5 V ADC, RSSI < 1.2 V
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    return b

def sfp_cage(b, name, td, rd, vcc='+3V3'):
    """SFP/SFP+ cage, own I2C bus; RS0/RS1 (OLT modules: Rx_Reset / RSSI trigger, 330 ohm for old pin-9-grounded modules)
    through series R so the FPGA keeps them hi-Z until the module is identified."""
    b.block = f'sfp:{name}'
    t, r = f'+3V3_{name}T', f'+3V3_{name}R'
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
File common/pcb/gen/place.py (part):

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        lay.place(drivers[tx], w - 5.0, y - 8.0, 270, True)   # bottom, on the TX can's axis: outputs (pins 13-18) face its leads
        laser_cell(lay, drivers[tx], tx)
        lay.place(tps[rx], rx_x - 5.0, y + 7.5, 0, True)  # APD bias south-west of the RX can, on the bottom with its parts
        cap = part_on(lay, f'{rx}APD_CAP', 'C')            # its CAP pin is boxed in by its neighbours' tracks: the capacitor at the pin, north of the diode
        px, py = pad_of_net(lay, tps[rx], f'{rx}APD_CAP')
        lay.place_pad(cap, next(n for n, v in lay.parts[cap].conns.items() if v == f'{rx}APD_CAP'), px + 1.25, py - 0.8, (1, 0))
        lay.track(f'{rx}APD_CAP', [(px, py), (px + 0.45, py), (px + 1.25, py - 0.8)], 0.2, pcbnew.B_Cu)
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def laser_cell(lay, driver, p):
    """The laser current's parts between the driver's output pins and the TX can: the series resistors in a row south
    of their pins, each dummy-load diode beside its resistor; the input pair's termination north of its pins; the three
    current-setting resistors at their pins (IMAX east, MODSET / BIASSET west). Their tracks are laid here: straight,
    and clear of the via each VCC pin between them needs."""
    def wire(net, r, x, y, toward, jog):
        pin = pad_of_net(lay, driver, net)
        lay.place_pad(r, next(n for n, v in lay.parts[r].conns.items() if v == net), x, y, toward)
        lay.track(net, [pin, (pin[0], y - jog), (x, y)], lay.bd.serdes_w, pcbnew.B_Cu)
    for pin, dx, dy, toward in (('IMAX', 1.5, 0, (0, 1)), ('MODSET', -1.0, 0.2, (-1, 0)), ('BIASSET', -1.0, -0.2, (-1, 0))):
        net = f'{p}LD_{pin}'
        (x, y), r = pad_of_net(lay, driver, net), part_on(lay, net, 'R')
        lay.place_pad(r, next(n for n, v in lay.parts[r].conns.items() if v == net), x + dx, y + dy, toward)
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    u = refs(lay, 'SY88236L')[0]
    pin = lambda n: lay.pad_xy(u, n)
    cap = lambda net: pad_of_net(lay, part_on(lay, net, 'C'), net)
    tp, tn, a, b = cap('ONU_TD_P'), cap('ONU_TD_N'), pin('7'), pin('6')
    hand_pair(lay, 'ONU_TD_P', [tp, (tp[0], a[1] - 1.0), (tp[0] + 1.0, a[1]), (a[0] - 0.6, a[1]), a], 1)
    hand_pair(lay, 'ONU_TD_N', [tn, (tn[0], a[1] - 2.0), (tn[0] + 1.0, a[1] - 1.0), (b[0] - 1.3, a[1] - 1.0), (b[0] - 0.8, b[1]), b], 2)
    rp, rn, c, d = cap('ONU_RD_P'), cap('ONU_RD_N'), pin('31'), pin('30')
    yp, yn = rp[1] + 1.5, rn[1] + 1.1
    hand_pair(lay, 'ONU_RD_P', [rp, (rp[0], yp), (rp[0] + c[1] - 1.56 - yp, c[1] - 1.56), (c[0], c[1] - 1.56), c], 1)
    hand_pair(lay, 'ONU_RD_N', [rn, (rn[0], yn), (rn[0] + c[1] - 2.56 - yn, c[1] - 2.56), (d[0], c[1] - 2.56), d], 1)
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
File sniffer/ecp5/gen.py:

#!/usr/bin/env python3
# SPDX-License-Identifier: CERN-OHL-S-2.0
"""Writes the ECP5 build inputs derived from code: dcu_params.vh (the DCUA parameters, one table for both lanes)
and sniffer.lpf (every pin's ball read from the routed card). Usage: gen.py <board.kicad_pcb> <out dir>"""
import re
import sys

# 2.48832 Gb/s from the 155.52 MHz VCXO: x16, no divider; 20-bit words (1:2 gear) at 124.416 MHz.
# Values after LiteICLink's serdes_ecp5.py (10BSER, hardware-proven), raw: no 8b10b, comma, word aligner or CTC.
DUAL = {
    'D_MACROPDB': '0b1', 'D_IB_PWDNB': '0b1', 'D_TXPLL_PWDNB': '0b1',
    'D_REFCK_MODE': '0b010', 'D_TX_MAX_RATE': '2.5', 'D_TX_VCO_CK_DIV': '0b000',
    'D_BITCLK_LOCAL_EN': '0b1',
    'D_CMUSETBIASI': '0b00', 'D_CMUSETI4CPP': '0d3', 'D_CMUSETI4CPZ': '0d3', 'D_CMUSETI4VCO': '0b00',
    'D_CMUSETICP4P': '0b01', 'D_CMUSETICP4Z': '0b101', 'D_CMUSETINITVCT': '0b00', 'D_CMUSETISCL4VCO': '0b000',
    'D_CMUSETP1GM': '0b000', 'D_CMUSETP2AGM': '0b000', 'D_CMUSETZGM': '0b000', 'D_SETIRPOLY_AUX': '0b01',
    'D_SETICONST_AUX': '0b01', 'D_SETIRPOLY_CH': '0b01', 'D_SETICONST_CH': '0b10', 'D_SETPLLRC': '0d1',
    'D_RG_EN': '0b0', 'D_RG_SET': '0b00', 'D_REQ_ISET': '0b011', 'D_PD_ISET': '0b11',
    'D_LOW_MARK': '0d4', 'D_HIGH_MARK': '0d12',
}
LANE = {
    'PROTOCOL': '10BSER', 'UC_MODE': '0b1', 'ENC_BYPASS': '0b1', 'DEC_BYPASS': '0b1', 'CTC_BYPASS': '0b1',
    'LSM_DISABLE': '0b1', 'ENABLE_CG_ALIGN': '0b0', 'WA_BYPASS': '0b1',
    'RPWDNB': '0b1', 'REQ_EN': '0b0', 'RX_RATE_SEL': '0d10', 'RTERM_RX': '0d19', 'RXIN_CM': '0b11',
    'RXTERM_CM': '0b11', 'CDR_MAX_RATE': '2.5', 'RX_DCO_CK_DIV': '0b000', 'RX_GEAR_MODE': '0b1',
    'FF_RX_H_CLK_EN': '0b1', 'FF_RX_F_CLK_DIS': '0b1', 'SEL_SD_RX_CLK': '0b1',
    'AUTO_FACQ_EN': '0b1', 'AUTO_CALIB_EN': '0b1', 'PDEN_SEL': '0b1',  # phase detector off on LOS
    'DCOATDCFG': '0b00', 'DCOATDDLY': '0b00', 'DCOBYPSATD': '0b1', 'DCOCALDIV': '0b000', 'DCOCTLGI': '0b011',
    'DCODISBDAVOID': '0b0', 'DCOFLTDAC': '0b00', 'DCOFTNRG': '0b001', 'DCOIOSTUNE': '0b010', 'DCOITUNE': '0b00',
    'DCOITUNE4LSB': '0b010', 'DCOIUPDNX2': '0b1', 'DCONUOFLSB': '0b100', 'DCOSCALEI': '0b01',
    'DCOSTARTVAL': '0b010', 'DCOSTEP': '0b11',
    'RLOS_SEL': '0b1', 'RX_LOS_EN': '0b1', 'RX_LOS_LVL': '0b100', 'RX_LOS_CEQ': '0b11',
    # TX: only CH0's, for its clock (the VCXO domain); the pins are open on the card
    'TPWDNB': '0b0', 'TX_GEAR_MODE': '0b1', 'FF_TX_H_CLK_EN': '0b1', 'FF_TX_F_CLK_DIS': '0b1',
    'RTERM_TX': '0d19', 'TXAMPLITUDE': '0d400',
}
PER_LANE = {0: {'TPWDNB': '0b1'}, 1: {}}
# a transmitter in use, after LiteICLink: slices 0, 2 and 3 on the main data
TX_ON = {'TPWDNB': '0b1', 'TDRV_SLICE0_CUR': '0b011', 'TDRV_SLICE0_SEL': '0b01', 'TDRV_SLICE1_CUR': '0b000',
         'TDRV_SLICE1_SEL': '0b00', 'TDRV_SLICE2_CUR': '0b11', 'TDRV_SLICE2_SEL': '0b01', 'TDRV_SLICE3_CUR': '0b10',
         'TDRV_SLICE3_SEL': '0b01', 'TDRV_SLICE4_CUR': '0b00', 'TDRV_SLICE4_SEL': '0b00', 'TDRV_SLICE5_CUR': '0b00',
         'TDRV_SLICE5_SEL': '0b00'}

PINS = re.compile(r'^(FWD_CLK|DS\d+|US\d+)_S$|^(VCXO_PWM|DS_SD)$')
SERDES = ['DS_RX_P', 'DS_RX_N', 'US_RX_P', 'US_RX_N', 'REFCLK_P', 'REFCLK_N'] # dedicated pads: no IO type


def board_pins(pcb, wanted=lambda net: PINS.match(net) or net in SERDES):
    """ECP5 ball of each wanted net, from the footprint with the LFE5UM value."""
    text = open(pcb).read()
    at = text.find('LFE5UM')
    if at < 0:
        sys.exit(f'{pcb}: no LFE5UM footprint')
    start = text.rfind('(footprint ', 0, at)
    depth, end = 0, start
    for end in range(start, len(text)):
        depth += {'(': 1, ')': -1}.get(text[end], 0)
        if depth == 0:
            break
    pads = re.findall(r'\(pad "([A-Z0-9]+)".*?\(net (?:\d+ )?"([^"]+)"\)', text[start:end], re.S)
    return {net: ball for ball, net in pads if wanted(net)}


def port(net):
    """Top-level port of a net: DS3_S -> DS_S[3]."""
    m = re.match(r'^(DS|US)(\d+)_S$', net)
    return f'{m[1]}_S[{m[2]}]' if m else net


def write_params(out, per_lane):
    """dcu_params.vh: the shared tables, then each lane's own settings."""
    params = dict(DUAL)
    for lane, extra in per_lane.items():
        params.update({f'CH{lane}_{k}': v for k, v in dict(LANE, **extra).items()})
    with open(f'{out}/dcu_params.vh', 'w') as f:
        f.write(',\n'.join(f'  .{k}("{v}")' for k, v in params.items()) + '\n')


def main(pcb, out):
    pins = board_pins(pcb)
    want = ['FWD_CLK_S', 'VCXO_PWM', 'DS_SD'] + [f'DS{i}_S' for i in range(16)] + [f'US{i}_S' for i in range(8)]
    missing = [n for n in want + SERDES if n not in pins]
    if missing:
        sys.exit(f'{pcb}: no ECP5 ball for {missing}')
    with open(f'{out}/sniffer.lpf', 'w') as f:
        for net in want:
            f.write(f'LOCATE COMP "{port(net)}" SITE "{pins[net]}";\n')
            f.write(f'IOBUF PORT "{port(net)}" IO_TYPE=LVCMOS33;\n')
        for net in SERDES:
            f.write(f'LOCATE COMP "{net}" SITE "{pins[net]}";\n')
        f.write('FREQUENCY NET "ref_clk" 124.416 MHZ;\nFREQUENCY NET "ds_clk" 124.416 MHZ;\n'
                'FREQUENCY NET "out_clk" 77.76 MHZ;\n')
    write_params(out, PER_LANE)


if __name__ == '__main__':
    if len(sys.argv) != 3:
        sys.exit(__doc__)
    main(*sys.argv[1:])
